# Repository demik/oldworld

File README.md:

# oldworld
Development ressources for vintage computing (Mostly "Old World" 68k and NuBus PPC Macintosh)

This is my sandbox repository. Once project has reached a quality level that feel adequate, they are moved to their own repo.

### Finished
A few projects are useable as is:
- [68k-nano+](/EDA/68k-nano+): Variant of the 68k-nano board by Matt Sarnoff 
- [68k-nano-wd](/EDA/68k-nano-wd): Minimalistic watchdog for the 68k-nano(+)
- [ADBDB](/EDA/ADBDB): Apple Desktop Bus developer/debug board 
- [Design68](/EDA/Design68): 65% DIY mechanical keyboard using AppleDesign controllers
- [NUBUSPAS16-DB](/EDA/NUBUSPAS16-DB): Daughter board for the MediaVision NuBus PAS 16
- [PAL16R LART](/EDA/PAL16R%20LART): PAL16R small helper PCB for reversing PAL16Rs 
- [SIMM72BL](/EDA/SIMM72BL): SIMM72 memory module interposer/debug board
- [VIA PLCC2DIP](/EDA/VIA%20PLCC2DIP): Simple PLCC to DIP 6522 VIA Adapter
- [VIA Pus](/EDA/VIA%20Plus): Macintosh 128k/512k/Plus diagnostic board replacing the VIA

### Moved
Theses have been moved to their own repositories
- [Quack](https://github.com/demik/quack): Bluetooth and ADB Mouse Converter for some old Apple computers
- [MacSnap SCSI](https://github.com/demik/MacSnap-SCSI): SCSI Card for the Macintosh 512Ke

Other stuff is WIP

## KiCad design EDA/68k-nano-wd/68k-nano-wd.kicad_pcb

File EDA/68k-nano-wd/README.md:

# 68k nano watchdog

Minimalistic watchdog build around an ATtiny45 for the 68k-nano(+).

## Features

- generate an external 10 Hz interrupt for FUZIX if running without an RTC
- monitor RAM accesses and enable a LED if no access have been done for a few seconds (crash)

## Hardware

The 68k nano watchdog hardware is very simple and straightforward. It can be built on a
breadboard as well.

### Building it

#### BOM

| Reference(s)          | Value      | Quantity | Notes                                  | Part number           |
|-----------------------|------------|----------|----------------------------------------|-----------------------|
| D2                    | -          | 1        | 5mm THT red LED                        |                       |
| D1                    | -          | 1        | 5mm THT color LED (other color)        |                       |
| C1, C2                | 100nF      | 1        | axial ceramic capacitor 3.8x2.6mm      | KEMET C412C104K5R5TA  |
| J5, J6                | 2x25       | 1        | 2x25 pins socket 2.54mm pitch          |                       |
| R1, R3                | 1kΩ+       | 2        | standard 1/4W carbon resistor for LEDs |                       |
| SW1                   | OFF-(ON)   | 1        | standard tactile button switch (6mm)   |                       |
| U1                    | ATtiny45   | 1        | 8-bit Microcontrollers - MCU           | ATTINY45-20PU         |
| U2                    | CD40107    | 1        | Logic Gates Dual 2-Input NAND          | CD40107BE             |

As of this writing (June 2026), all components are available from major distributors like [Mouser](https://mouser.com) and [Jameco](https://jameco.com).

All parts are through-hole for that extra vintage feel.

The gerbers files can be downloaded from the [releases section](https://github.com/demik/oldworld/releases/download/68k-nano%2B%2Fv1P/68k_nano_watchdog.zip)

#### Code

The MCU code is inside the ATtiny45 directory. There is a pretty much complete Makefile here (type make help)

You will also need avr-gcc

## Additional information

You may need some programer for the ATtiny45

## About

Open hardware, released under the terms of the 3-clause BSD license.

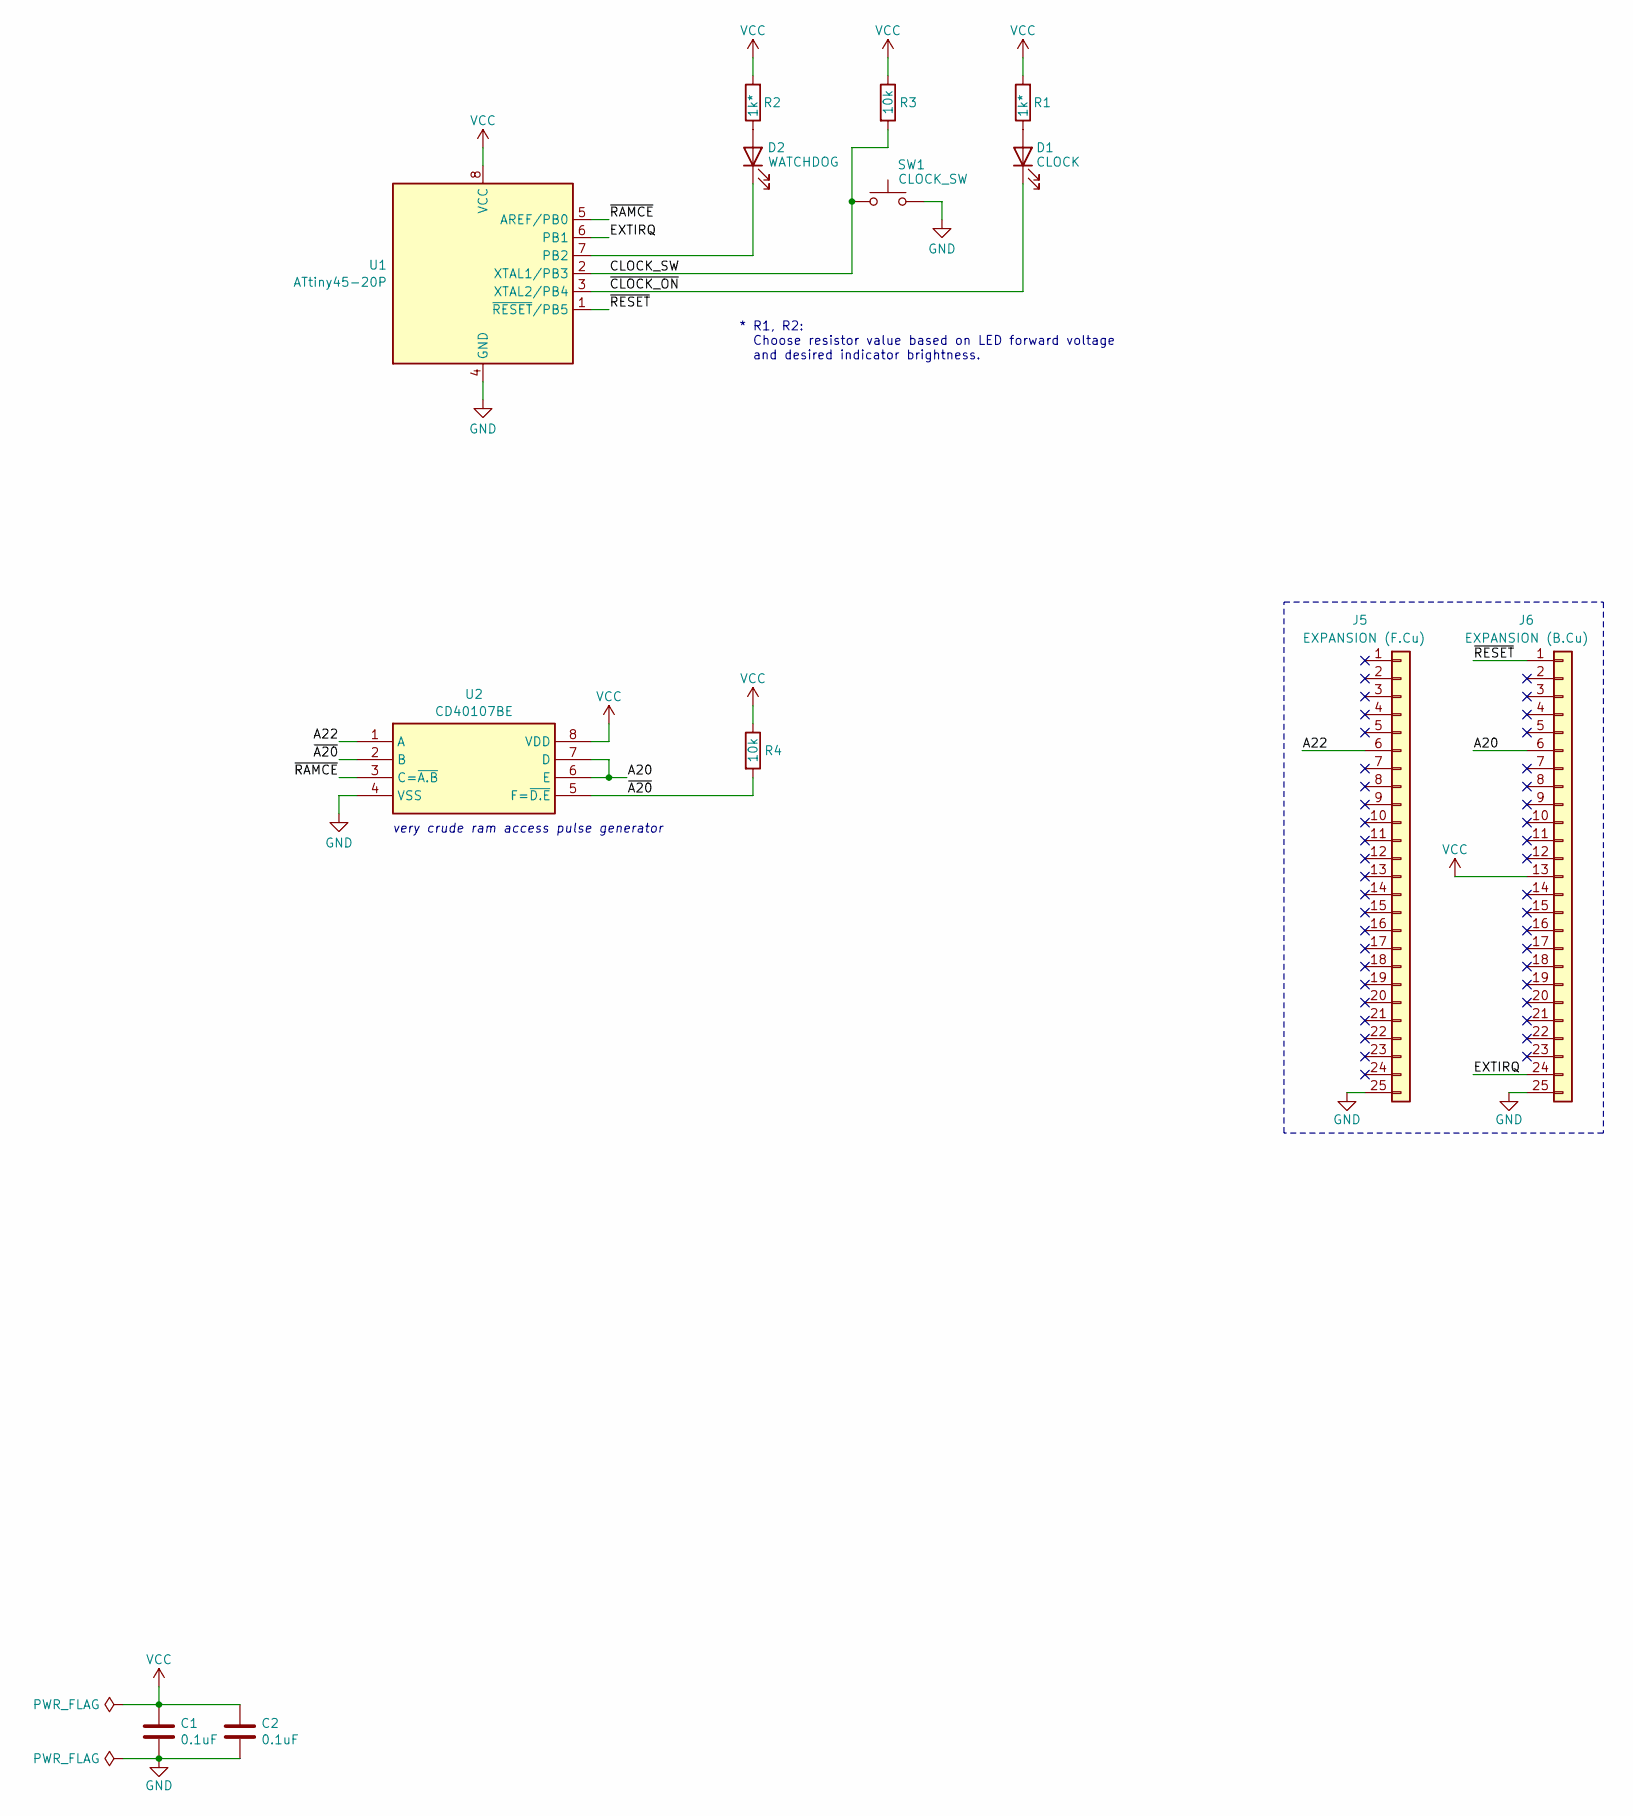
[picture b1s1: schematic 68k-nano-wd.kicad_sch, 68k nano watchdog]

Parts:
C1, C2: 0.1uF; C_Rect_L7.0mm_W2.0mm_P5.00mm
D1: CLOCK; LED_D5.0mm
D2: WATCHDOG; LED_D5.0mm
J5: EXPANSION (F.Cu); PinSocket_1x25_P2.54mm_Vertical
J6: EXPANSION (B.Cu); PinSocket_1x25_P2.54mm_Vertical
R1, R2: 1k*; R_Axial_DIN0204_L3.6mm_D1.6mm_P7.62mm_Horizontal
R3, R4: 10k; R_Axial_DIN0204_L3.6mm_D1.6mm_P7.62mm_Horizontal
SW1: CLOCK_SW; SW_PUSH_6mm
U1: ATtiny45-20P; DIP-8_W7.62mm
U2: CD40107BE; DIP-8_W7.62mm; Mouser Part Number 595-CD40107BE

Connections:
/A20: J6.6, U2.6 (E), U2.7 (D)
/A22: J5.6, U2.1 (A)
/CLOCK_SW: R3.2, SW1.1, U1.2 (XTAL1/PB3)
/EXTIRQ: J6.24, U1.6 (PB1)
/~A20: R4.2, U2.2 (B), U2.5 (F=~D.E)
/~CLOCK_ON: D1.1 (K), U1.3 (XTAL2/PB4)
/~RAMCE: U1.5 (AREF/PB0), U2.3 (C=~A.B)
/~RESET: J6.1, U1.1 (~RESET/PB5)
GND: C1.2, C2.2, J5.25, J6.25, SW1.2, U1.4 (GND), U2.4 (VSS)
unnamed: D1.2 (A), R1.1
unnamed: D2.2 (A), R2.1
unnamed: D2.1 (K), U1.7 (PB2)
VCC: C1.1, C2.1, J6.13, R1.2, R2.2, R3.1, R4.1, U1.8 (VCC), U2.8 (VDD)

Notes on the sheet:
* R1, R2: Choose resistor value based on LED forward voltage and desired indicator brightness.
very crude ram access pulse generator

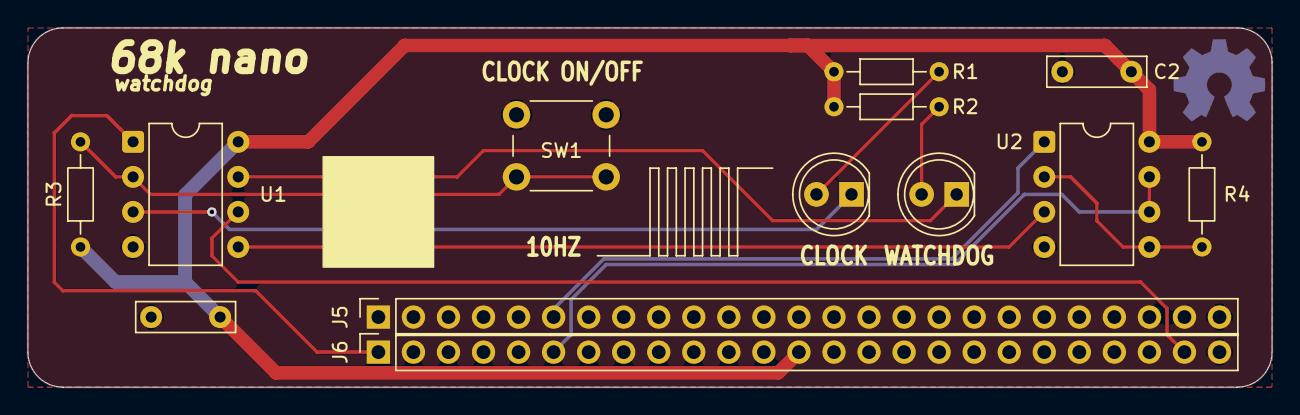
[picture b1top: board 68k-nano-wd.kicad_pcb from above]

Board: 2 copper layers, 90.2 x 26.0 mm, 13 parts (0 on the bottom side), 13 nets.

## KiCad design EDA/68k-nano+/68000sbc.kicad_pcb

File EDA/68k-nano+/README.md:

# 68k nano+

A minimal single-board computer based on the venerable ["Texas Cockroach"](https://youtu.be/UaHtGf4aRLs?t=2074)
Motorola 68000 16/32-bit microprocessor.

This is a variant from the original that Matt Sarnoff designed and published ["here"](https://github.com/74hc595/68k-nano). 

It was created to use 16550 UARTs in PLCC-44 form that are avaiable brand new instead of playing the lottery with old parts (the DIP variant from the original board isn't manufactured anymore)

There is also a small memorymap helper which tiddy up the memory map (see below). It is totally optional.

This variant is named 68k-nano+ (because of the PLCC socket and the extra memory helper) to differentiate it from the original one.

## Features

- 68HC000 processor running at 12MHz
- 1MB RAM
- 64KB ROM
- 16550 UART providing a 5V FTDI serial port
- 44-pin IDE connector for CompactFlash card adapter
- Connector for SparkFun DS3234 real-time clock
- Only two 74HC glue logic chips required

It chas been tested with [FUZIX](https://codeberg.org/EtchedPixels/FUZIX) and is running just fine. You can of course run the original ROM.

## Hardware

The 68k nano(+) hardware is simple and straightforward. It can be built on a
breadboard (though there may be stability issues at higher clock speeds).

### Memory map

Due to the minimal address decoding circuitry, accessing certain memory regions will cause multiple devices to be selected. This should be avoided.

#### Original memory map

```
$000000-0xFFFF     ROM (repeats 16 times)
$100000-1FFFFF  X  Forbidden (multiple devices selected)
$200000-2FFFFF     ROM (mirror of $000000-0FFFFF)
$300000-$7FFFF  X  Forbidden (multiple devices selected)
$800000-8FFFFF     Open bus (available for expansion)
$900000-9xxxxF     CompactFlash card
$A00000-AxxxxF     UART
$B00000-BFFFFF  X  Forbidden (multiple devices selected)
$C00000-CFFFFF     RAM
$D00000-DFFFFF  X  Forbidden (multiple devices selected)
$E00000-EFFFFF     RAM (mirror of $C00000-CFFFFF)
$F00000-FFFFFF  X  Forbidden (multiple devices selected)
```

This is summarized with the following equations:

```
/ROMSEL  = /A23
/RAMSEL  =  A22
/UARTSEL =  A23 * /A22 * A21
/CARDSEL =  A20
```

#### Extended memory map (with helper)

This change the original memory map above from 

````
000000-0fffff	ROM 
100000-1fffff	ROM CARD 
200000-2fffff	ROM 
300000-3fffff	ROM CARD 
400000-4fffff	ROM RAM 
500000-5fffff	ROM RAM CARD 
600000-6fffff	ROM RAM 
700000-7fffff	ROM RAM CARD 
800000-8fffff	
900000-9fffff	CARD 
a00000-afffff	UART 
b00000-bfffff	UART CARD 
c00000-cfffff	RAM 
d00000-dfffff	RAM CARD 
e00000-efffff	RAM 
f00000-ffffff	RAM CARD 
````

to

````
000000-0fffff	ROM 
100000-1fffff	ROM CARD 
200000-2fffff	ROM 
300000-3fffff	ROM CARD 
400000-4fffff	ROM RAM 
500000-5fffff	ROM 
600000-6fffff	ROM RAM 
700000-7fffff	ROM 
800000-8fffff	
900000-9fffff	CARD 
a00000-afffff	UART 
b00000-bfffff	UART CARD 
c00000-cfffff	RAM 
d00000-dfffff	
e00000-efffff	RAM 
f00000-ffffff
````

Two new IO ranges are now avaiable. They can be used for example to extend the memory area to 2MB using an external board.

### Building it

`bom.txt` contains a bill of materials. As of this writing (June 2026), all components are available from major distributors like [Mouser](https://mouser.com) and [Jameco](https://jameco.com). If purchasing 68000s from eBay, note that [vintage
ICs are a common target of counterfeiters](https://medium.com/supplyframe-hardware/the-underground-parts-store-identifying-counterfeit-computer-chips-3020adbb01f7).

All parts are through-hole for that extra vintage feel. Note that some of the decoupling capacitors (C4, C5, C6, C8, and C10) are underneath ICs, so open-frame IC sockets are required. Large IC sockets can also be expensive (_especially_ DIP-64 sockets!) so a cheaper alternative is to use [breakaway SIP 0.1" machine-pin headers](https://www.amazon.com/dp/B0187LTEX2/ref=cm_sw_em_r_mt_dp_U_M5IbFbVJ3NVDH).

To keep the board in this spirit with the PLCC-64 UART, you will also need a PLCC-44 THT socket.

For the ROMs U5 and U7, [Aries 28-526-10 low-profile ZIF sockets](https://www.jameco.com/shop/ProductDisplay?catalogId=10001&langId=-1&storeId=10001&productId=102745) will fit, but _barely_. The release latch may scrape against the RAM IC to its north, but Matt found that it's not a huge deal. I can confirm that statement. If you can afford the Aries sockets, go for them.

You can use either a full-can or half-can oscillator for X1. Check the original README.md or FUZIX build instructions if the clock is something other than 12 MHz.

The 44-pin IDE header accepts a CompactFlash adapter board such as [this one](https://www.amazon.com/gp/product/B07Y2MTS13), available from Amazon and other vendors.

Some adapters are male, so you will need a matching female socket on the board. `bom.txt` contains a few parts number for this.

If not using the additional memory helper, do not populate R8, R9 and U9. Jumer two wires, _do not short both_, following to the markings on the silkscreen:

- U9 pin 3 to U9 pin 6
- U9 pin 2 to U9 pin 5

The gerbers files can be downloaded from the [releases section](https://github.com/demik/oldworld/releases/download/68k-nano%2B%2Fv1P/68k_nano+_1P.zip)

## Additional information

For more information, please check the original [README.md](https://github.com/74hc595/68k-nano/blob/master/README.md)

## About

Open hardware, released under the terms of the 3-clause BSD license.

Copyright 2020-2026 Matt Sarnoff.
Modified by demik in 2026.

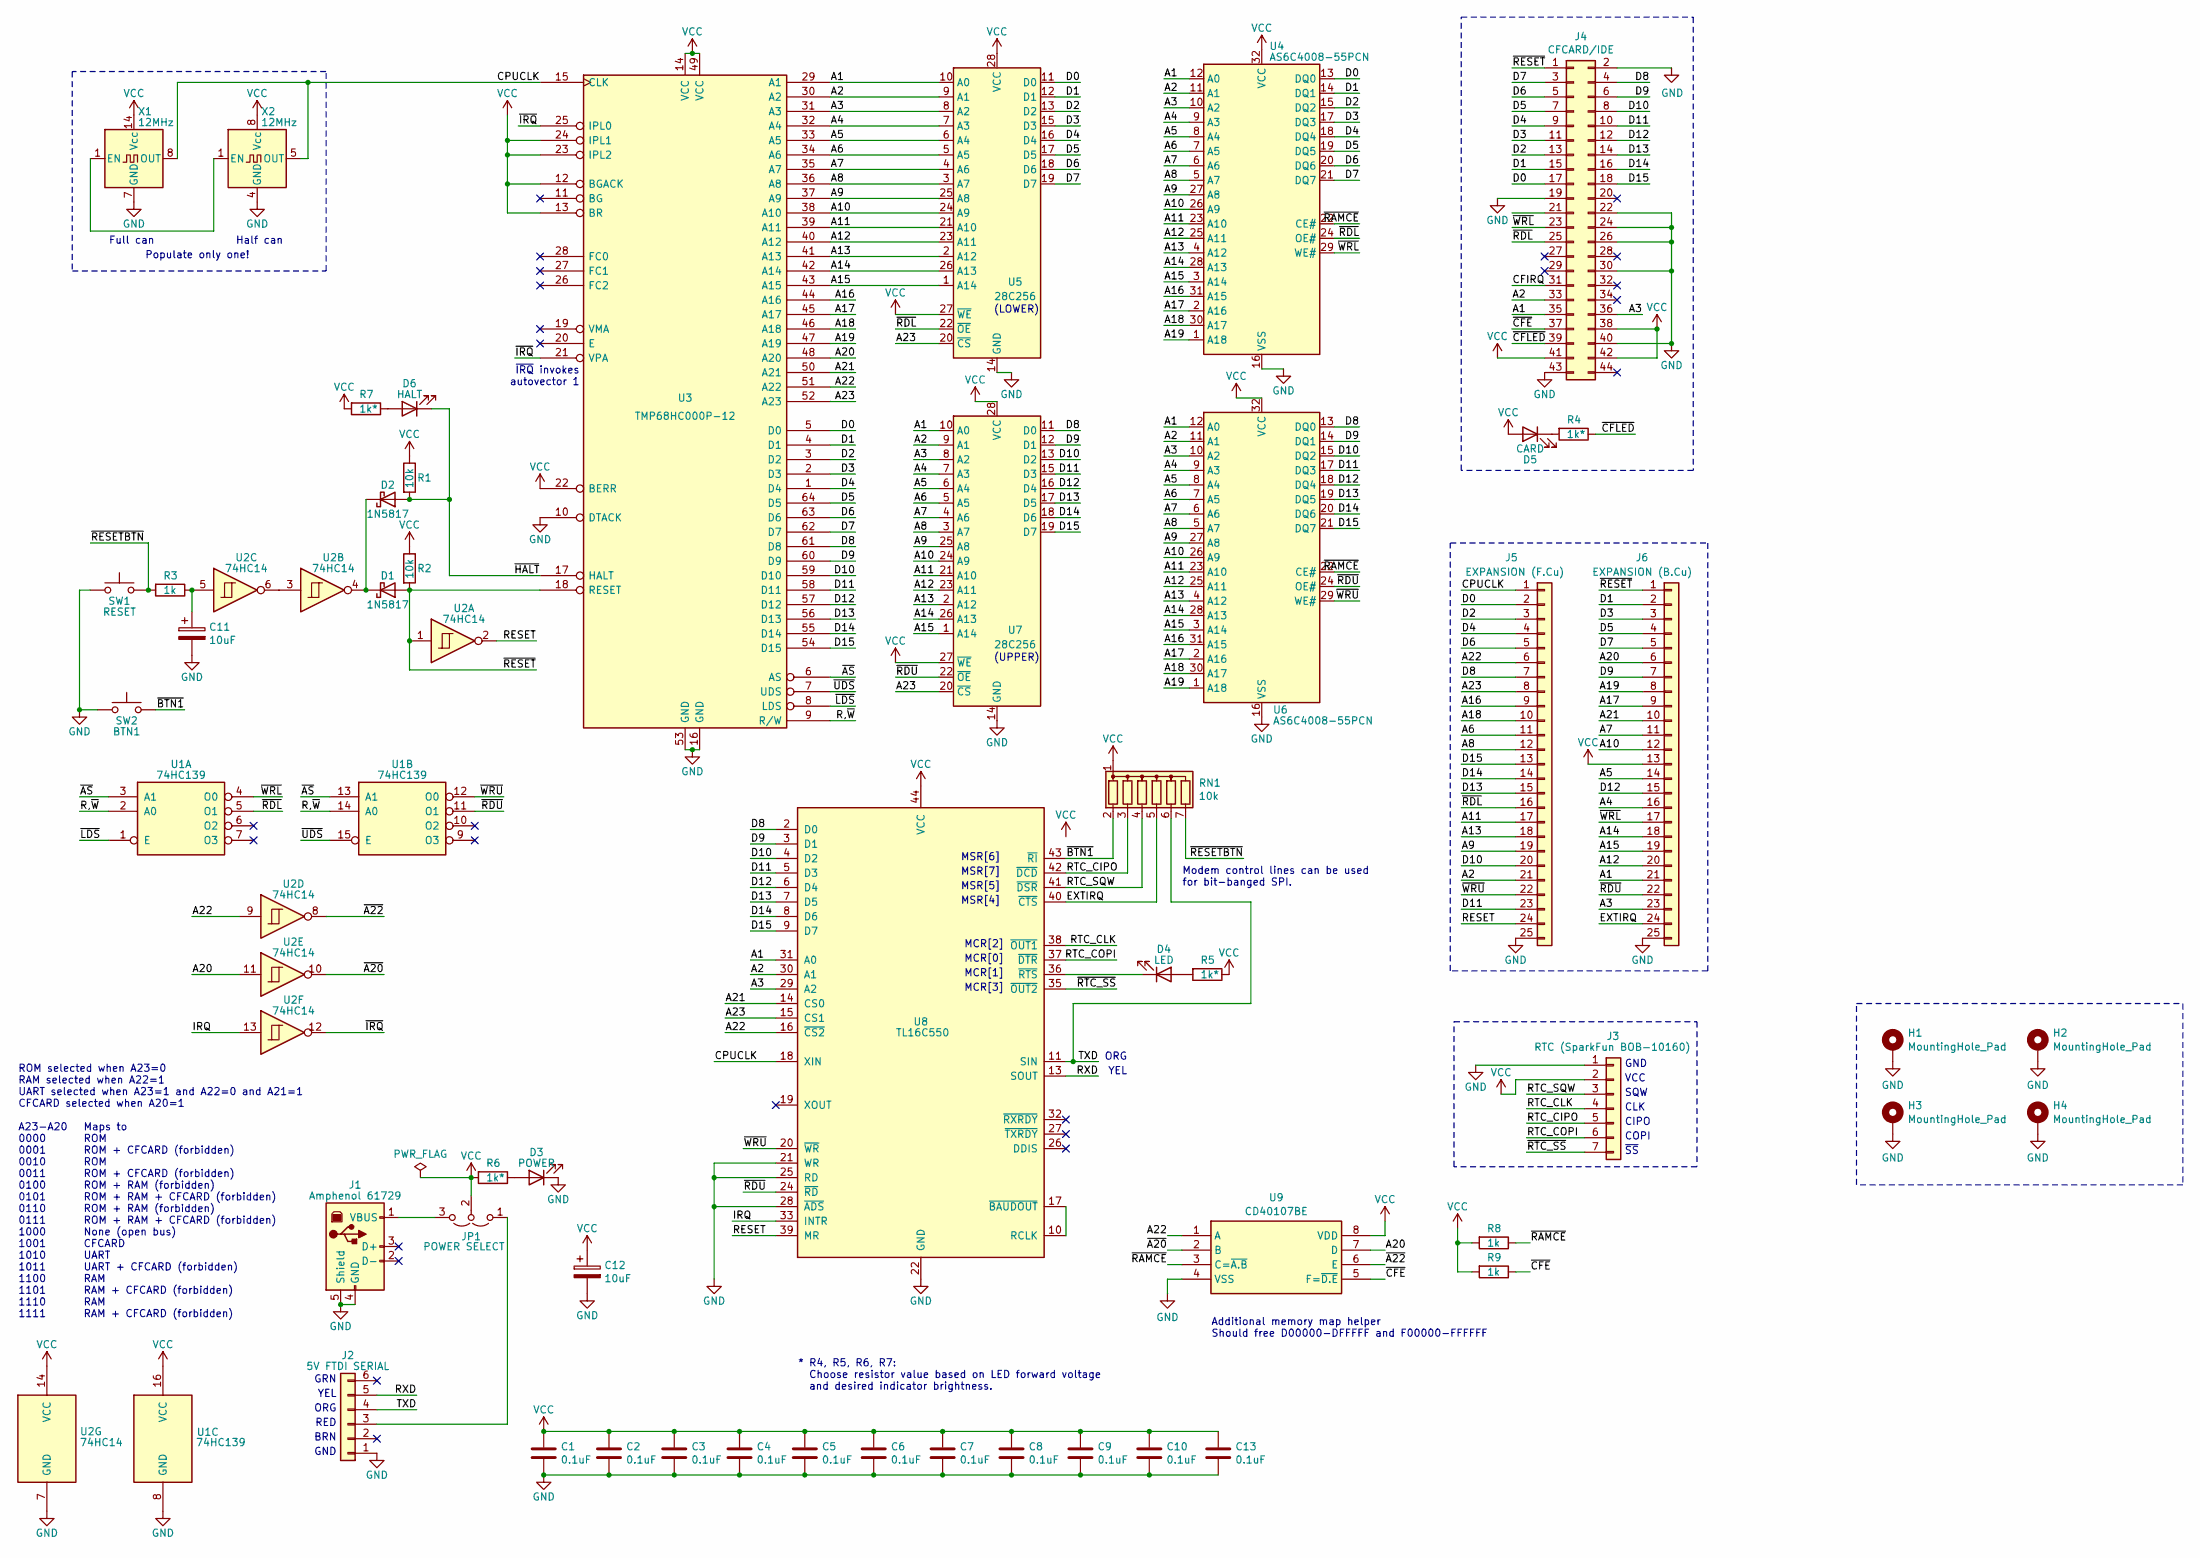
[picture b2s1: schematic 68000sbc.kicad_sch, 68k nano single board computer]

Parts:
C1, C2, C3, C4, C5, C6, C7, C8, C9, C10, C13: 0.1uF; C_Rect_L7.0mm_W2.0mm_P5.00mm
C11, C12: 10uF; CP_Radial_D5.0mm_P2.50mm
D1, D2: 1N5817; D_DO-35_SOD27_P7.62mm_Horizontal
D3: POWER; LED_D5.0mm
D4: LED; LED_D5.0mm
D5: CARD; LED_D5.0mm
D6: HALT; LED_D5.0mm
H1, H2, H3, H4: MountingHole_Pad; MountingHole_2.7mm_M2.5_ISO7380_Pad
J1: Amphenol 61729; USB_B_Lumberg_2411_02_Horizontal
J2: 5V FTDI SERIAL; PinHeader_1x06_P2.54mm_Horizontal
J3: RTC (SparkFun BOB-10160); PinHeader_1x07_P2.54mm_Vertical
J4: CFCARD/IDE; PinHeader_2x22_P2.00mm_Vertical
J5: EXPANSION (F.Cu); PadRow_1x25_P2.54mm
J6: EXPANSION (B.Cu); PadRow_1x25_P2.54mm
JP1: POWER SELECT; PinHeader_1x03_P2.54mm_Vertical
R1, R2: 10k; R_Axial_DIN0204_L3.6mm_D1.6mm_P7.62mm_Horizontal
R3, R8, R9: 1k; R_Axial_DIN0204_L3.6mm_D1.6mm_P7.62mm_Horizontal
R4, R5, R6, R7: 1k*; R_Axial_DIN0204_L3.6mm_D1.6mm_P7.62mm_Horizontal
RN1: 10k; R_Array_SIP7
SW1: RESET; SW_PUSH_6mm
SW2: BTN1; SW_PUSH_6mm
U1: 74HC139; DIP-16_W7.62mm_Socket
U2: 74HC14; DIP-14_W7.62mm_Socket
U3: TMP68HC000P-12; DIP-64_W22.86mm_Socket
U4, U6: AS6C4008-55PCN; DIP-32_W15.24mm_Socket
U5, U7: 28C256; DIP-28_W15.24mm_Socket
U8: TL16C550; PLCC-44_THT-Socket
U9: CD40107BE; DIP-8_W7.62mm; Mouser Part Number 595-CD40107BE
X1: 12MHz; Oscillator_DIP-14
X2: 12MHz; Oscillator_DIP-8

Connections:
/A1: J4.35, J6.21, U3.29 (A1), U4.12 (A0), U5.10 (A0), U6.12 (A0), U7.10 (A0), U8.31 (A0)
/A2: J4.33, J5.21, U3.30 (A2), U4.11 (A1), U5.9 (A1), U6.11 (A1), U7.9 (A1), U8.30 (A1)
/A3: J4.36, J6.23, U3.31 (A3), U4.10 (A2), U5.8 (A2), U6.10 (A2), U7.8 (A2), U8.29 (A2)
/A4: J6.16, U3.32 (A4), U4.9 (A3), U5.7 (A3), U6.9 (A3), U7.7 (A3)
/A5: J6.14, U3.33 (A5), U4.8 (A4), U5.6 (A4), U6.8 (A4), U7.6 (A4)
/A6: J5.11, U3.34 (A6), U4.7 (A5), U5.5 (A5), U6.7 (A5), U7.5 (A5)
/A7: J6.11, U3.35 (A7), U4.6 (A6), U5.4 (A6), U6.6 (A6), U7.4 (A6)
/A8: J5.12, U3.36 (A8), U4.5 (A7), U5.3 (A7), U6.5 (A7), U7.3 (A7)
/A9: J5.19, U3.37 (A9), U4.27 (A8), U5.25 (A8), U6.27 (A8), U7.25 (A8)
/A10: J6.12, U3.38 (A10), U4.26 (A9), U5.24 (A9), U6.26 (A9), U7.24 (A9)
/A11: J5.17, U3.39 (A11), U4.23 (A10), U5.21 (A10), U6.23 (A10), U7.21 (A10)
/A12: J6.20, U3.40 (A12), U4.25 (A11), U5.23 (A11), U6.25 (A11), U7.23 (A11)
/A13: J5.18, U3.41 (A13), U4.4 (A12), U5.2 (A12), U6.4 (A12), U7.2 (A12)
/A14: J6.18, U3.42 (A14), U4.28 (A13), U5.26 (A13), U6.28 (A13), U7.26 (A13)
/A15: J6.19, U3.43 (A15), U4.3 (A14), U5.1 (A14), U6.3 (A14), U7.1 (A14)
/A16: J5.9, U3.44 (A16), U4.31 (A15), U6.31 (A15)
/A17: J6.9, U3.45 (A17), U4.2 (A16), U6.2 (A16)
/A18: J5.10, U3.46 (A18), U4.30 (A17), U6.30 (A17)
/A19: J6.8, U3.47 (A19), U4.1 (A18), U6.1 (A18)
/A20: J6.6, U2.11, U3.48 (A20), U9.7 (D)
/A21: J6.10, U3.50 (A21), U8.14 (CS0)
/A22: J5.6, U2.9, U3.51 (A22), U8.16 (~CS2), U9.1 (A)
/A23: J5.8, U3.52 (A23), U5.20 (~CS), U7.20 (~CS), U8.15 (CS1)
/CFIRQ: J4.31
/CPUCLK: J5.1, U3.15 (CLK), U8.18 (XIN), X1.8 (OUT), X2.5 (OUT)
/D0: J4.17, J5.2, U3.5 (D0), U4.13 (DQ0), U5.11 (D0)
/D1: J4.15, J6.2, U3.4 (D1), U4.14 (DQ1), U5.12 (D1)
/D2: J4.13, J5.3, U3.3 (D2), U4.15 (DQ2), U5.13 (D2)
/D3: J4.11, J6.3, U3.2 (D3), U4.17 (DQ3), U5.15 (D3)
/D4: J4.9, J5.4, U3.1 (D4), U4.18 (DQ4), U5.16 (D4)
/D5: J4.7, J6.4, U3.64 (D5), U4.19 (DQ5), U5.17 (D5)
/D6: J4.5, J5.5, U3.63 (D6), U4.20 (DQ6), U5.18 (D6)
/D7: J4.3, J6.5, U3.62 (D7), U4.21 (DQ7), U5.19 (D7)
/D8: J4.4, J5.7, U3.61 (D8), U6.13 (DQ0), U7.11 (D0), U8.2 (D0)
/D9: J4.6, J6.7, U3.60 (D9), U6.14 (DQ1), U7.12 (D1), U8.3 (D1)
/D10: J4.8, J5.20, U3.59 (D10), U6.15 (DQ2), U7.13 (D2), U8.4 (D2)
/D11: J4.10, J5.23, U3.58 (D11), U6.17 (DQ3), U7.15 (D3), U8.5 (D3)
/D12: J4.12, J6.15, U3.57 (D12), U6.18 (DQ4), U7.16 (D4), U8.6 (D4)
/D13: J4.14, J5.15, U3.56 (D13), U6.19 (DQ5), U7.17 (D5), U8.7 (D5)
/D14: J4.16, J5.14, U3.55 (D14), U6.20 (DQ6), U7.18 (D6), U8.8 (D6)
/D15: J4.18, J5.13, U3.54 (D15), U6.21 (DQ7), U7.19 (D7), U8.9 (D7)
/EXTIRQ: J6.24, RN1.5 (R4), U8.40 (~CTS)
/IRQ: U2.13, U8.33 (INTR)
/R,~W: U1.2 (A0), U1.14 (A0), U3.9 (R/W)
/RESET: J5.24, U2.2, U8.39 (MR)
/RTC_CIPO: J3.5, RN1.3 (R2), U8.42 (~DCD)
/RTC_CLK: J3.4, U8.38 (~OUT1)
/RTC_COPI: J3.6, U8.37 (~DTR)
/RTC_SQW: J3.3, RN1.4 (R3), U8.41 (~DSR)
/RXD: J2.5, U8.13 (SOUT)
/TXD: J2.4, RN1.6 (R5), U8.11 (SIN)
/~A20: U2.10, U9.2 (B)
/~A22: U2.8, U9.6 (E)
/~AS: U1.3 (A1), U1.13 (A1), U3.6 (AS)
/~BTN1: RN1.2 (R1), SW2.2, U8.43 (~RI)
/~CFE: J4.37, R9.1, U9.5 (F=~D.E)
/~CFLED: J4.39, R4.1
/~HALT: D2.2 (A), D6.1 (K), R1.2, U3.17 (HALT)
/~IRQ: U2.12, U3.21 (VPA), U3.25 (IPL0)
/~LDS: U1.1 (E), U3.8 (LDS)
/~RAMCE: R8.1, U4.22 (CE#), U6.22 (CE#), U9.3 (C=~A.B)
/~RDL: J4.25, J5.16, U1.5 (O1), U4.24 (OE#), U5.22 (~OE)
/~RDU: J6.22, U1.11 (O1), U6.24 (OE#), U7.22 (~OE), U8.24 (~RD)
/~RESETBTN: R3.2, RN1.7 (R6), SW1.2
/~RESET: D1.2 (A), J4.1, J6.1, R2.2, U2.1, U3.18 (RESET)
/~RTC_SS: J3.7, U8.35 (~OUT2)
/~UDS: U1.15 (E), U3.7 (UDS)
/~WRL: J4.23, J6.17, U1.4 (O0), U4.29 (WE#)
/~WRU: J5.22, U1.12 (O0), U6.29 (WE#), U8.20 (~WR)
GND: C1.2, C2.2, C3.2, C4.2, C5.2, C6.2, C7.2, C8.2, C9.2, C10.2, C11.2, C12.2, C13.2, D3.1 (K), H1.1, H2.1, H3.1, H4.1, J1.4 (GND), J1.5 (Shield), J1.SH (Shield), J2.1, J3.1, J4.2, J4.19, J4.22, J4.24, J4.26, J4.30, J4.40, J4.43, J5.25, J6.25, SW1.1, SW2.1, U1.8 (GND), U2.7 (GND), U3.10 (DTACK), U3.16 (GND), U3.53 (GND), U4.16 (VSS), U5.14 (GND), U6.16 (VSS), U7.14 (GND), U8.21 (WR), U8.22 (GND), U8.25 (RD), U8.28 (~ADS), U9.4 (VSS), X1.7 (GND), X2.4 (GND)
unnamed: C11.1, R3.1, U2.5
unnamed: D1.1 (K), D2.1 (K), U2.4
unnamed: D3.2 (A), R6.1
unnamed: D4.2 (A), R5.2
unnamed: D4.1 (K), U8.36 (~RTS)
unnamed: D5.1 (K), R4.2
unnamed: D6.2 (A), R7.1
unnamed: J1.1 (VBUS), JP1.3 (B)
unnamed: J2.3, JP1.1 (A)
unnamed: U2.3, U2.6
unnamed: U8.10 (RCLK), U8.17 (~BAUDOUT)
unnamed: X1.1 (EN), X2.1 (EN)
VCC: C1.1, C2.1, C3.1, C4.1, C5.1, C6.1, C7.1, C8.1, C9.1, C10.1, C12.1, C13.1, D5.2 (A), J3.2, J4.38, J4.41, J4.42, J6.13, JP1.2 (C), R1.1, R2.1, R5.1, R6.2, R7.2, R8.2, R9.2, RN1.1 (common), U1.16 (VCC), U2.14 (VCC), U3.12 (BGACK), U3.13 (BR), U3.14 (VCC), U3.22 (BERR), U3.23 (IPL2), U3.24 (IPL1), U3.49 (VCC), U4.32 (VCC), U5.27 (~WE), U5.28 (VCC), U6.32 (VCC), U7.27 (~WE), U7.28 (VCC), U8.44 (VCC), U9.8 (VDD), X1.14 (Vcc), X2.8 (Vcc)

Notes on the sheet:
* R4, R5, R6, R7: Choose resistor value based on LED forward voltage and desired indicator brightness.
ROM selected when A23=0 RAM selected when A22=1 UART selected when A23=1 and A22=0 and A21=1 CFCARD selected when A20=1
COPI
~{SS}
~{IRQ} invokes autovector 1
Maps to ROM ROM + CFCARD (forbidden) ROM ROM + CFCARD (forbidden) ROM + RAM (forbidden) ROM + RAM + CFCARD (forbidden) ROM + RAM (forbidden) ROM + RAM + CFCARD (forbidden) None (open bus) CFCARD UART UART + CFCARD (forbidden) RAM RAM + CFCARD (forbidden) RAM RAM + CFCARD (forbidden)
MCR[1]
MSR[4]
GND
VCC
MSR[6]
A23-A20 0000 0001 0010 0011 0100 0101 0110 0111 1000 1001 1010 1011 1100 1101 1110 1111
Additional memory map helper Should free D00000-DFFFFF and F00000-FFFFFF
CLK
MSR[7]
SQW
BRN
ORG
MSR[5]
(LOWER)
YEL
Half can
MCR[0]
(UPPER)
GRN
MCR[2]
Populate only one!
MCR[3]
RED
Full can
CIPO
Modem control lines can be used for bit-banged SPI.

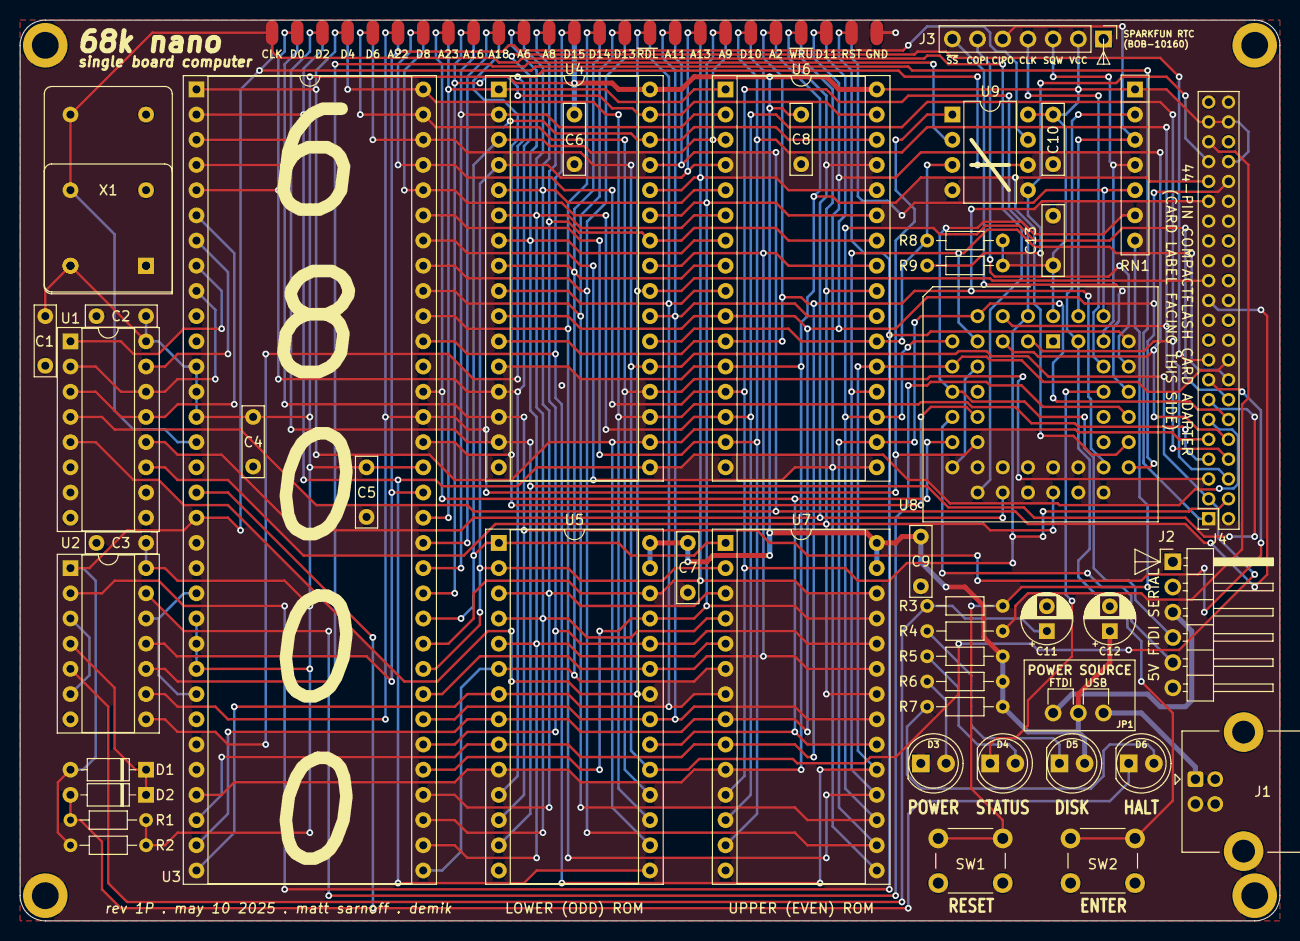
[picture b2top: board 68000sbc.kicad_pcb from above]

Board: 2 copper layers, 127.0 x 90.8 mm, 53 parts (1 on the bottom side), 82 nets.

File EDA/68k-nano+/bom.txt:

Ref     Part                                            Distributor SKU
----------------------------------------------------------------------------------------------------------
C1-C10  0.1uF decoupling capacitor (ceramic/monolithic)
C11,C12 10uF electrolytic capacitor, 16V+
C13     0.1uF decoupling capacitor (ceramic/monolithic)
D1-D2   1N5817 Schottky diode (1N4148 also works)
D3-D6   5mm LED (your choice of color)
J1      USB-B PCB-mount right-angle connector           Jameco 2096245          Mouser 649-61729-1011BLF
J2      6-position 0.1" male right-angle header
J3      (optional) 7-position 0.1" header
J4      2x22 2mm header
JP1     3-position 0.1" male straight header + jumper
R1,R2   10k resistor, 1/4W
R3      1k resistor, 1/4W
R4-R7   Resistors for LEDs D3-D6 (330/1k)
RN1     10k bussed resistor network (SIP-7)                                     Mouser 652-4607X-1LF-10K
SW1,SW2 6mm tactile switch
U1      74HC139 dual 2-to-4 line decoder (DIP-16)                               Mouser 595-SN74HC139N
U2      74HC14 hex inverting Schmitt trigger (DIP-14)
U3      68000 microprocessor (DIP-64)                   Jameco 2288039
U4,U6   AS6C4008-55PCN 512Kx8 static RAM (DIP-32)       Jameco 242448           Mouser 913-AS6C4008-55PCN
U5,U7   AT28C256 32Kx8 EEPROM (DIP-28)                  Jameco 74843            Mouser 556-AT28C25615PU
U8      ST16C550 UART (PLCC-44)                                                 Mouser 701-ST16C550IJ44-F
        PLCC-44 THT socket (Amphenol 54020-44030LF)                             Mouser 649-54020-44030LF
X1      5V oscillator (DIP-8 or DIP-14)

Optional memory map helper
--------------------------
R8,R9   1k resistor, 1/4W
U9      CD40107BE (DIP-8)                                                       Mouser 595-CD40107BE

Optional peripherals
--------------------
Low profile ZIF-28 sockets for U5/U7 - Jameco 102745 (Aries 28-526-10)
SparkFun DeadOn RTC Breakout - https://www.sparkfun.com/products/10160
CompactFlash to 2.5" 44-pin IDE adapter - https://www.amazon.com/gp/product/B07Y2MTS13

Variant with angled CF and female connector:
3M Headers & Wire Housings 44P STRT socket - Mouser 150244-6002-RB (517-150244-6002-RB)
CompactFlash to 2.5" 44-pin IDE adapter - https://www.amazon.fr/Lecteur-carte-Compact-Flash-port/dp/B0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

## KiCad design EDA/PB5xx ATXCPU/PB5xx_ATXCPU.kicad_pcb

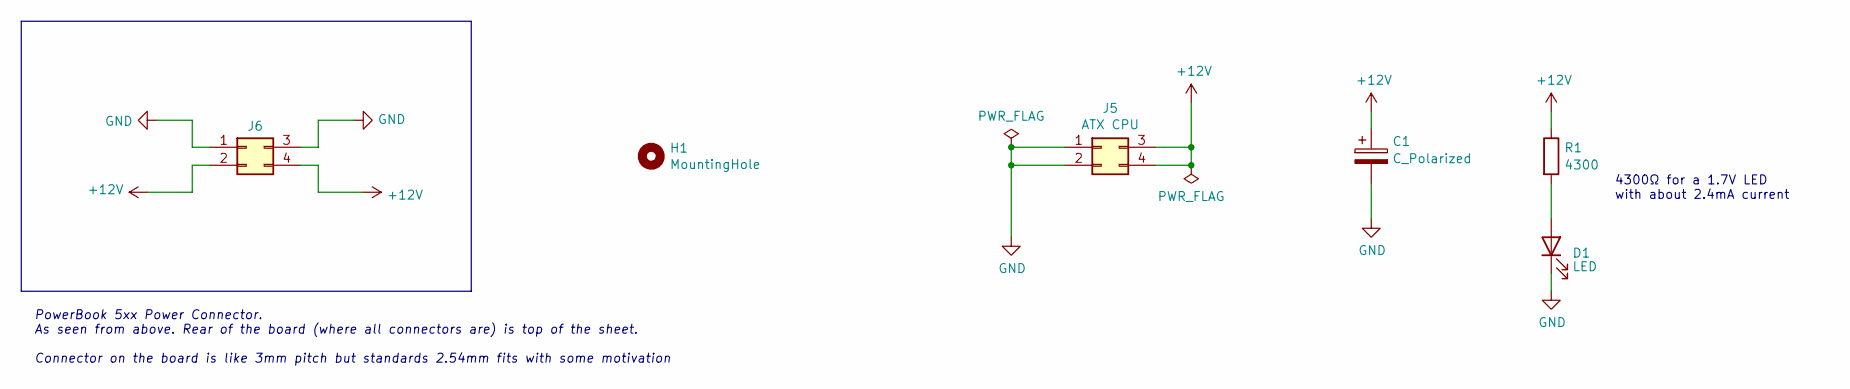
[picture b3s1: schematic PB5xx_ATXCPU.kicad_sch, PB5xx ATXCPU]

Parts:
C1: C_Polarized; CP_Radial_D8.0mm_P3.50mm
D1: LED; LED_D5.0mm
H1: MountingHole; MountingHole_3.2mm_M3
J5: ATX CPU; Molex_Mini-Fit_Jr_5569-04A2_2x02_P4.20mm_Horizontal
J6: Conn_02x02_Top_Bottom; PinSocket_2x02_P2.54mm_Vertical
R1: 4300; R_Axial_DIN0207_L6.3mm_D2.5mm_P7.62mm_Horizontal

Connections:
+12V: C1.1, J5.3, J5.4, J6.2, J6.4, R1.1
GND: C1.2, D1.1 (K), J5.1, J5.2, J6.1, J6.3
unnamed: D1.2 (A), R1.2

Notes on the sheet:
4300Ω for a 1.7V LED with about 2.4mA current
PowerBook 5xx Power Connector. As seen from above. Rear of the board (where all connectors are) is top of the sheet. Connector on the board is like 3mm pitch but standards 2.54mm fits with some motivation

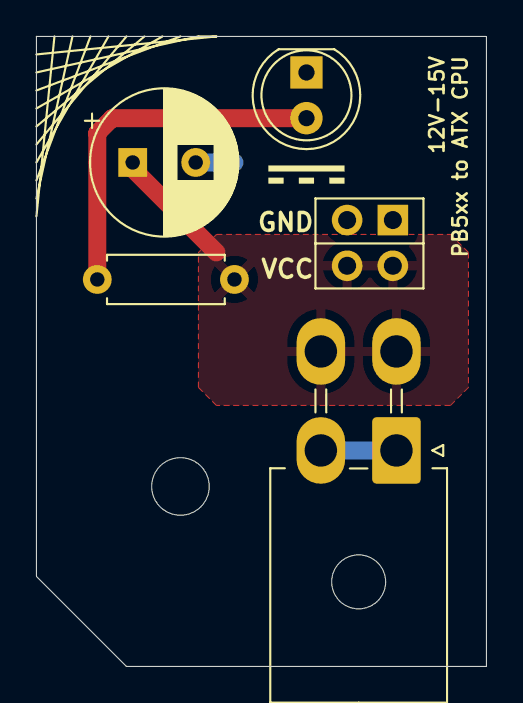
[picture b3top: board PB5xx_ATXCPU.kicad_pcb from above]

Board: 2 copper layers, 25.0 x 35.0 mm, 7 parts (1 on the bottom side), 3 nets.

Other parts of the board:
DC: LOGO

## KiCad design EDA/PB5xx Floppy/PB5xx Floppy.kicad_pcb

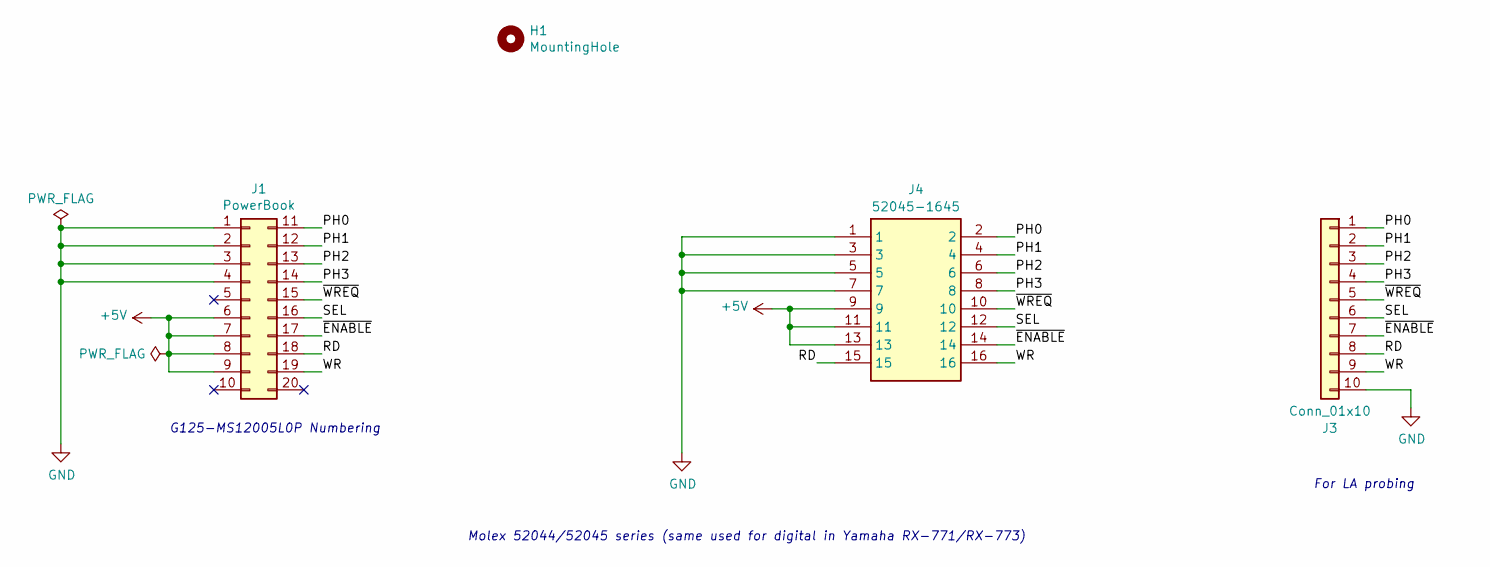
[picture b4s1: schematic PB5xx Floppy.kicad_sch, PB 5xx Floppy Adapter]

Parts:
H1: MountingHole; MountingHole_3.2mm_M3
J1: PowerBook; G125-MV12005L0P
J3: Conn_01x10; PinHeader_1x10_P2.54mm_Vertical
J4: 52045-1645; Mouser Part Number 538-52045-1545

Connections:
+5V: J1.6, J1.7, J1.8, J1.9, J4.9, J4.11, J4.13
/PH0: J1.11, J3.1, J4.2
/PH1: J1.12, J3.2, J4.4
/PH2: J1.13, J3.3, J4.6
/PH3: J1.14, J3.4, J4.8
/RD: J1.18, J3.8, J4.15
/SEL: J1.16, J3.6, J4.12
/WR: J1.19, J3.9, J4.16
/~ENABLE: J1.17, J3.7, J4.14
/~WREQ: J1.15, J3.5, J4.10
GND: J1.1, J1.2, J1.3, J1.4, J3.10, J4.1, J4.3, J4.5, J4.7

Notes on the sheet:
Molex 52044/52045 series (same used for digital in Yamaha RX-771/RX-773)
For LA probing
G125-MS12005L0P Numbering

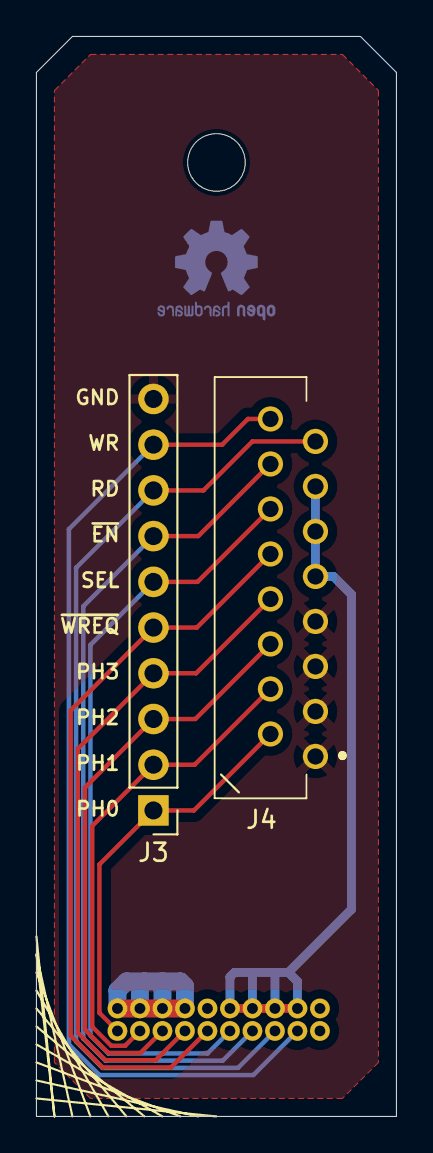
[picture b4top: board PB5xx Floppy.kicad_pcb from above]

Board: 2 copper layers, 20.0 x 60.0 mm, 4 parts (1 on the bottom side), 11 nets.

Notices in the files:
EDA/MacSnap SCSI/MacSnap SCSI.kicad_pcb:
MacSnap SCSI Reloaded © 2023 Michel Depeige
